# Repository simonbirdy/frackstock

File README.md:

# frackstock
LED walking stick  for the Frackwoche 2017 www.frackwoche.ch

The LED walking stick contains 100 WS2812B RGB-LEDs which can be adressed seperately. The walking stick can be controlled with a accelometer or remotely via a 968 MHz RF-Link. This allows a master to control all walking sticks in range 

Videos showing the walking stick in Action:

General Setup (Remote Control):

Android Device (WLAN) -> Sender (ESP2866 & RFM117) -> walking stick (RFM217 & STM32f0)

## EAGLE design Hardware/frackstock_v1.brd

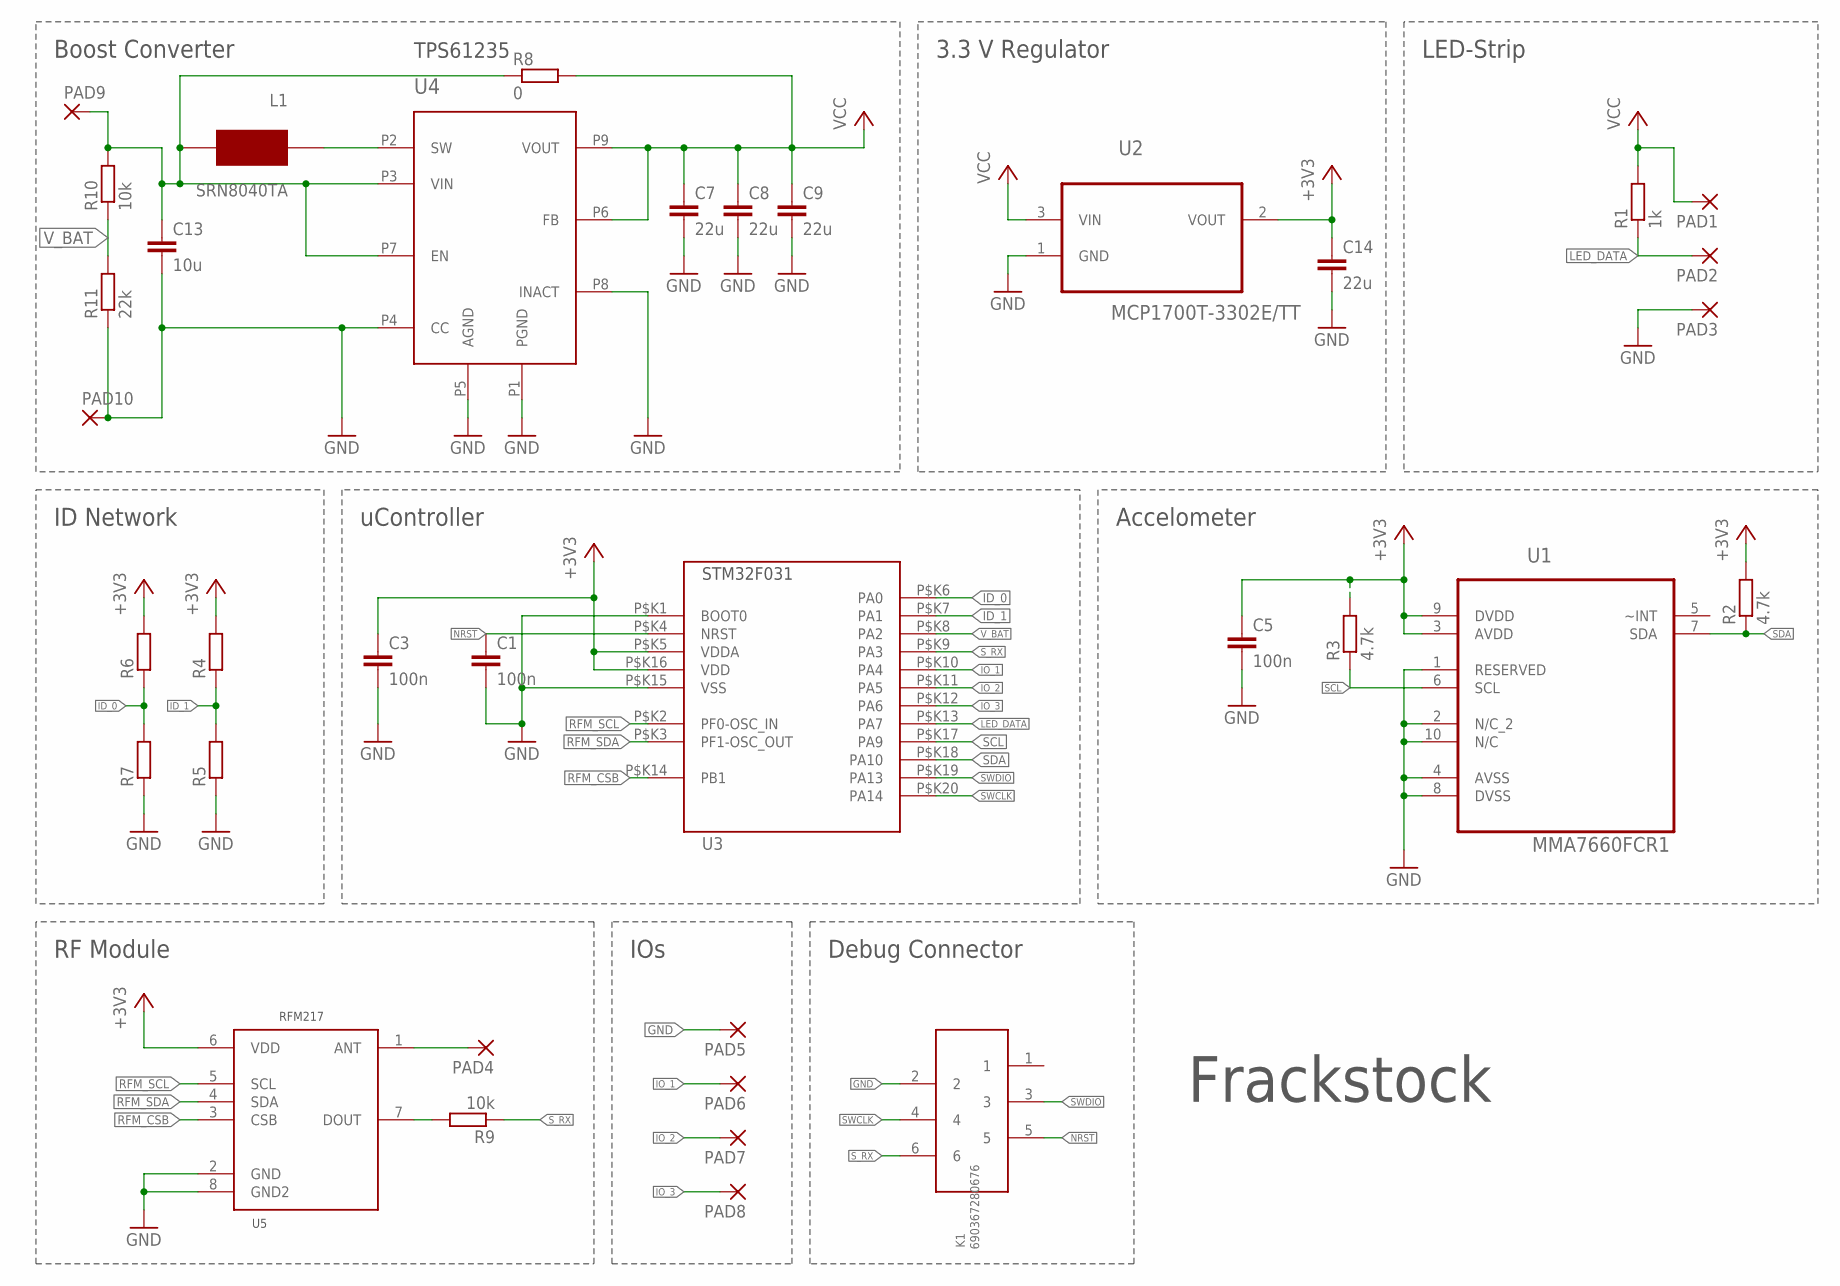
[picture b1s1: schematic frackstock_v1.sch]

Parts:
C1, C3, C5: 100n; C0603
C7, C8, C9: 22u; C0805
C13: 10u; C0805
C14: 22u; C0603
K1: 690367280676
L1: SRN8040TA; SRN8040TA_PACK
PAD1, PAD2, PAD3, PAD9, PAD10: SMD5; SMD2,54-5,08
PAD4, PAD5, PAD6, PAD7, PAD8: SMD2; SMD1,27-2,54
R1: 1k; R0603
R2, R3: 4.7k; R0603
R4, R5, R6, R7: R-EU_R0603; R0603
R8: 0; R1206
R9, R10: 10k; R0603
R11: 22k; R0603
U1: MMA7660FCR1; DFN300X300X100-10N
U2: MCP1700T-3302E/TT; SOT95P237X112-3N
U3: STM32F031; TSSOP20
U4: TPS61235; VQFN
U5: RFM217; RFM217_PACK

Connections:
+3V3: C3.1, C5.1, C14.1, R2.2, R3.2, R4.2, R6.2, U1.3 (AVDD), U1.9 (DVDD), U2.2 (VOUT), U3.P$K5 (VDDA), U3.P$K16 (VDD), U5.6 (VDD)
GND: C1.2, C3.2, C5.2, C7.2, C8.2, C9.2, C13.2, C14.2, K1.2, PAD3.1, PAD5.1, PAD10.1, R5.1, R7.1, R11.1, U1.1 (RESERVED), U1.2 (N/C_2), U1.4 (AVSS), U1.8 (DVSS), U1.10 (N/C), U2.1 (GND), U3.P$K1 (BOOT0), U3.P$K15 (VSS), U4.P1 (PGND), U4.P4 (CC), U4.P5 (AGND), U4.P8 (INACT), U5.2 (GND), U5.8 (GND2)
ID_0: R6.1, R7.2, U3.P$K6 (PA0)
ID_1: R4.1, R5.2, U3.P$K7 (PA1)
IO_1: PAD6.1, U3.P$K10 (PA4)
IO_2: PAD7.1, U3.P$K11 (PA5)
IO_3: PAD8.1, U3.P$K12 (PA6)
LED_DATA: PAD2.1, R1.1, U3.P$K13 (PA7)
unnamed: R9.2, U5.7 (DOUT)
unnamed: PAD4.1, U5.1 (ANT)
unnamed: L1.2, U4.P2 (SW)
unnamed: C13.1, L1.1, PAD9.1, R8.1, R10.2, U4.P3 (VIN), U4.P7 (EN)
NRST: C1.1, K1.5, U3.P$K4 (NRST)
RFM_CSB: U3.P$K14 (PB1), U5.3 (CSB)
RFM_SCL: U3.P$K2 (PF0-OSC_IN), U5.5 (SCL)
RFM_SDA: U3.P$K3 (PF1-OSC_OUT), U5.4 (SDA)
SCL: R3.1, U1.6 (SCL), U3.P$K17 (PA9)
SDA: R2.1, U1.7 (SDA), U3.P$K18 (PA10)
SWCLK: K1.4, U3.P$K20 (PA14)
SWDIO: K1.3, U3.P$K19 (PA13)
S_RX: K1.6, R9.1, U3.P$K9 (PA3)
VCC: C7.1, C8.1, C9.1, PAD1.1, R1.2, R8.2, U2.3 (VIN), U4.P6 (FB), U4.P9 (VOUT)
V_BAT: R10.1, R11.2, U3.P$K8 (PA2)

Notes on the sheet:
Frackstock
Boost Converter
3.3 V Regulator
LED-Strip
ID Network
uController
Debug Connector
IOs
RF Module
Accelometer

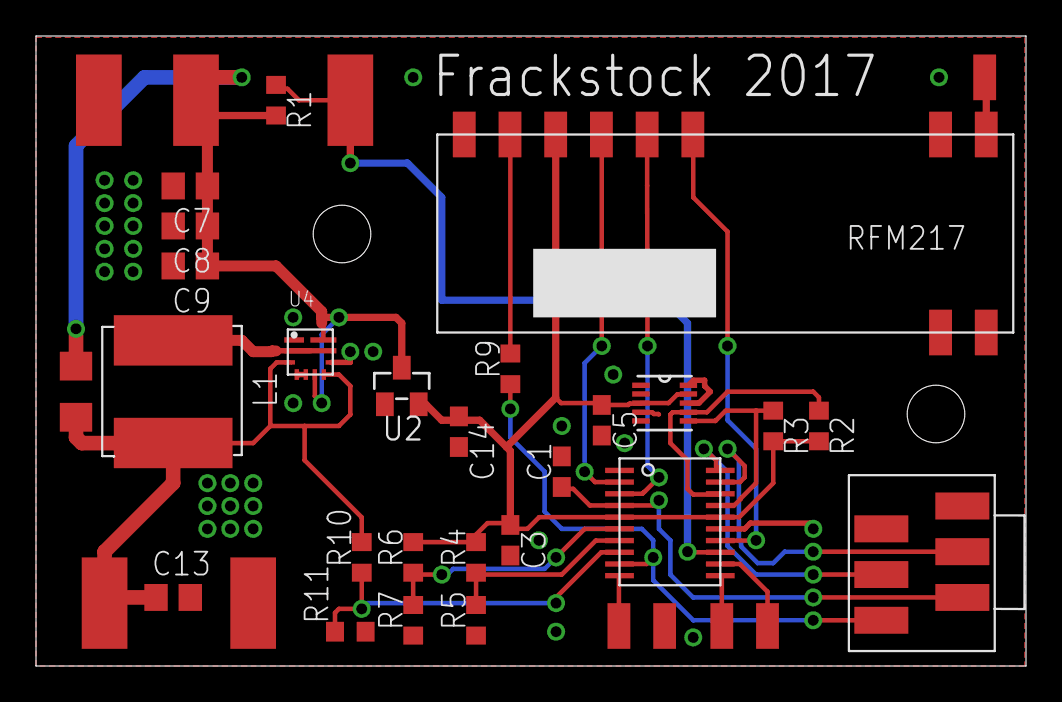
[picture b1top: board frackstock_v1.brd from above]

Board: 2 copper layers, 55.0 x 35.0 mm, 36 parts (0 on the bottom side), 23 nets.

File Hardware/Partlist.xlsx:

Part | Value | Device | Package | Library | Supplier | Order number | Price
U2 |  | MCP1700-T-3302 |  |  | Farnell | 1296592 | 0.34300000000000003 | 50
U4 |  | TPS61235 |  |  | Mouser | 595-TPS61235PRWLR | 1.8 | 5
U3 |  | STM32F031 |  |  | Farnell | 2503233 | 1.41 | 50
U1 |  | MMA7660FCR1 |  |  | Farnell | 2080493 | 1.24 | 40
U5 |  | RFM217 |  |  | vogelsi1 |  |  | 39
C7,C8,C9,C14 | 22uF / 10V | Kondensator | 805 |  | Mouser | 81-GRM188R61A226ME5D |  | 200
C13 | 10 uF / 10V | Kondensator | 805 |  | Mouser |  |  | 50
L1 | 1 uH | SRN80401A |  |  | Mouser | 652-SRN8040-1R0Y | 0.4 | 5
C1,C3,C5 | 100nF |  | 603 |  | Mouser | 81-GRM39X104K25 |  | 150
R1 | 1k |  | 603 |  | Mouser | 667-ERJ-1GEJ102C |  | 100
R2,R3 | 4.7k |  | 603 |  | Mouser | 667-ERJ-1GEJ472C |  | 100
R9,R10 | 10k |  | 603 |  | Mouser | 603-RC0201FR-0710KL |  | 100
R11 | 22k |  | 603 |  | Mouser | 603-RC0201FR-0722KL | 0.01 | 100
K1 |  |  |  |  | Farnell | 1565585 |  | -
 |  | Batteriehalter |  |  |  |  | 1.3

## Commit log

2017-03-13 removed doubled animation_cycle
2017-05-07 Hardware Added
    Added Schematic and knob design
    Software Receiver: Added Accel module
2017-07-20 Update Frackwoche Version
    Android Software
    Receiver Software

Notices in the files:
parts and their libraries:
Board_to_Board_Connectors_rev15d: Copyright: Würth Elektronik
